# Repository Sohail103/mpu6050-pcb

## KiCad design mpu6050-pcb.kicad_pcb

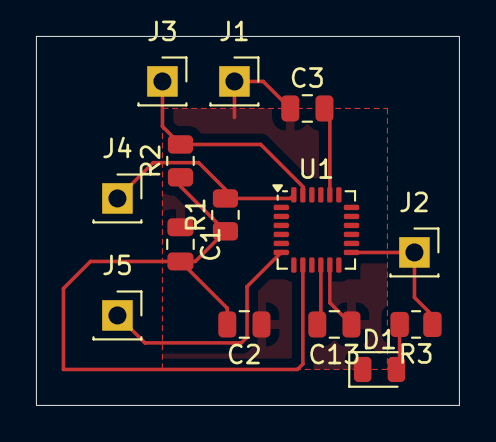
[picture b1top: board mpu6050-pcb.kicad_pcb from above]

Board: 2 copper layers, 23.5 x 20.5 mm, 14 parts (0 on the bottom side), 8 nets.

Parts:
C1: 0.01 uF; C_0805_2012Metric
C2, C13: 0.1 uF; C_0805_2012Metric
C3: 2200 pF; C_0805_2012Metric
D1: LED; LED_0805_2012Metric
J1, J2, J3, J4, J5: Conn_01x01_Socket; PinSocket_1x01_P2.54mm_Vertical
R1, R2: 4.7k; R_0805_2012Metric
R3: 1k; R_0805_2012Metric
U1: MPU-6050; InvenSense_QFN-24_4x4mm_P0.5mm

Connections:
3V3: C1.2, C2.2, J2.1, R1.1, R2.1, R3.1, U1.8 (VLOGIC), U1.13 (VDD)
GND: C1.1, C2.1, C3.1, C13.1, D1.1 (K), J1.1, U1.1 (CLKIN), U1.11 (FSYNC), U1.18 (GND)
unnamed: D1.2 (A), R3.2
unnamed: J3.1, R2.2, U1.23 (SCL)
unnamed: J4.1, R1.2, U1.24 (SDA)
unnamed: J5.1, U1.6 (AUX_DA)
unnamed: C3.2, U1.20 (CPOUT)
unnamed: C13.2, U1.10 (REGOUT)

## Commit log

2025-07-06 added schematic and started routing
2025-07-06 updated schematic and changed routing
2025-07-06 changed routing and connector type
